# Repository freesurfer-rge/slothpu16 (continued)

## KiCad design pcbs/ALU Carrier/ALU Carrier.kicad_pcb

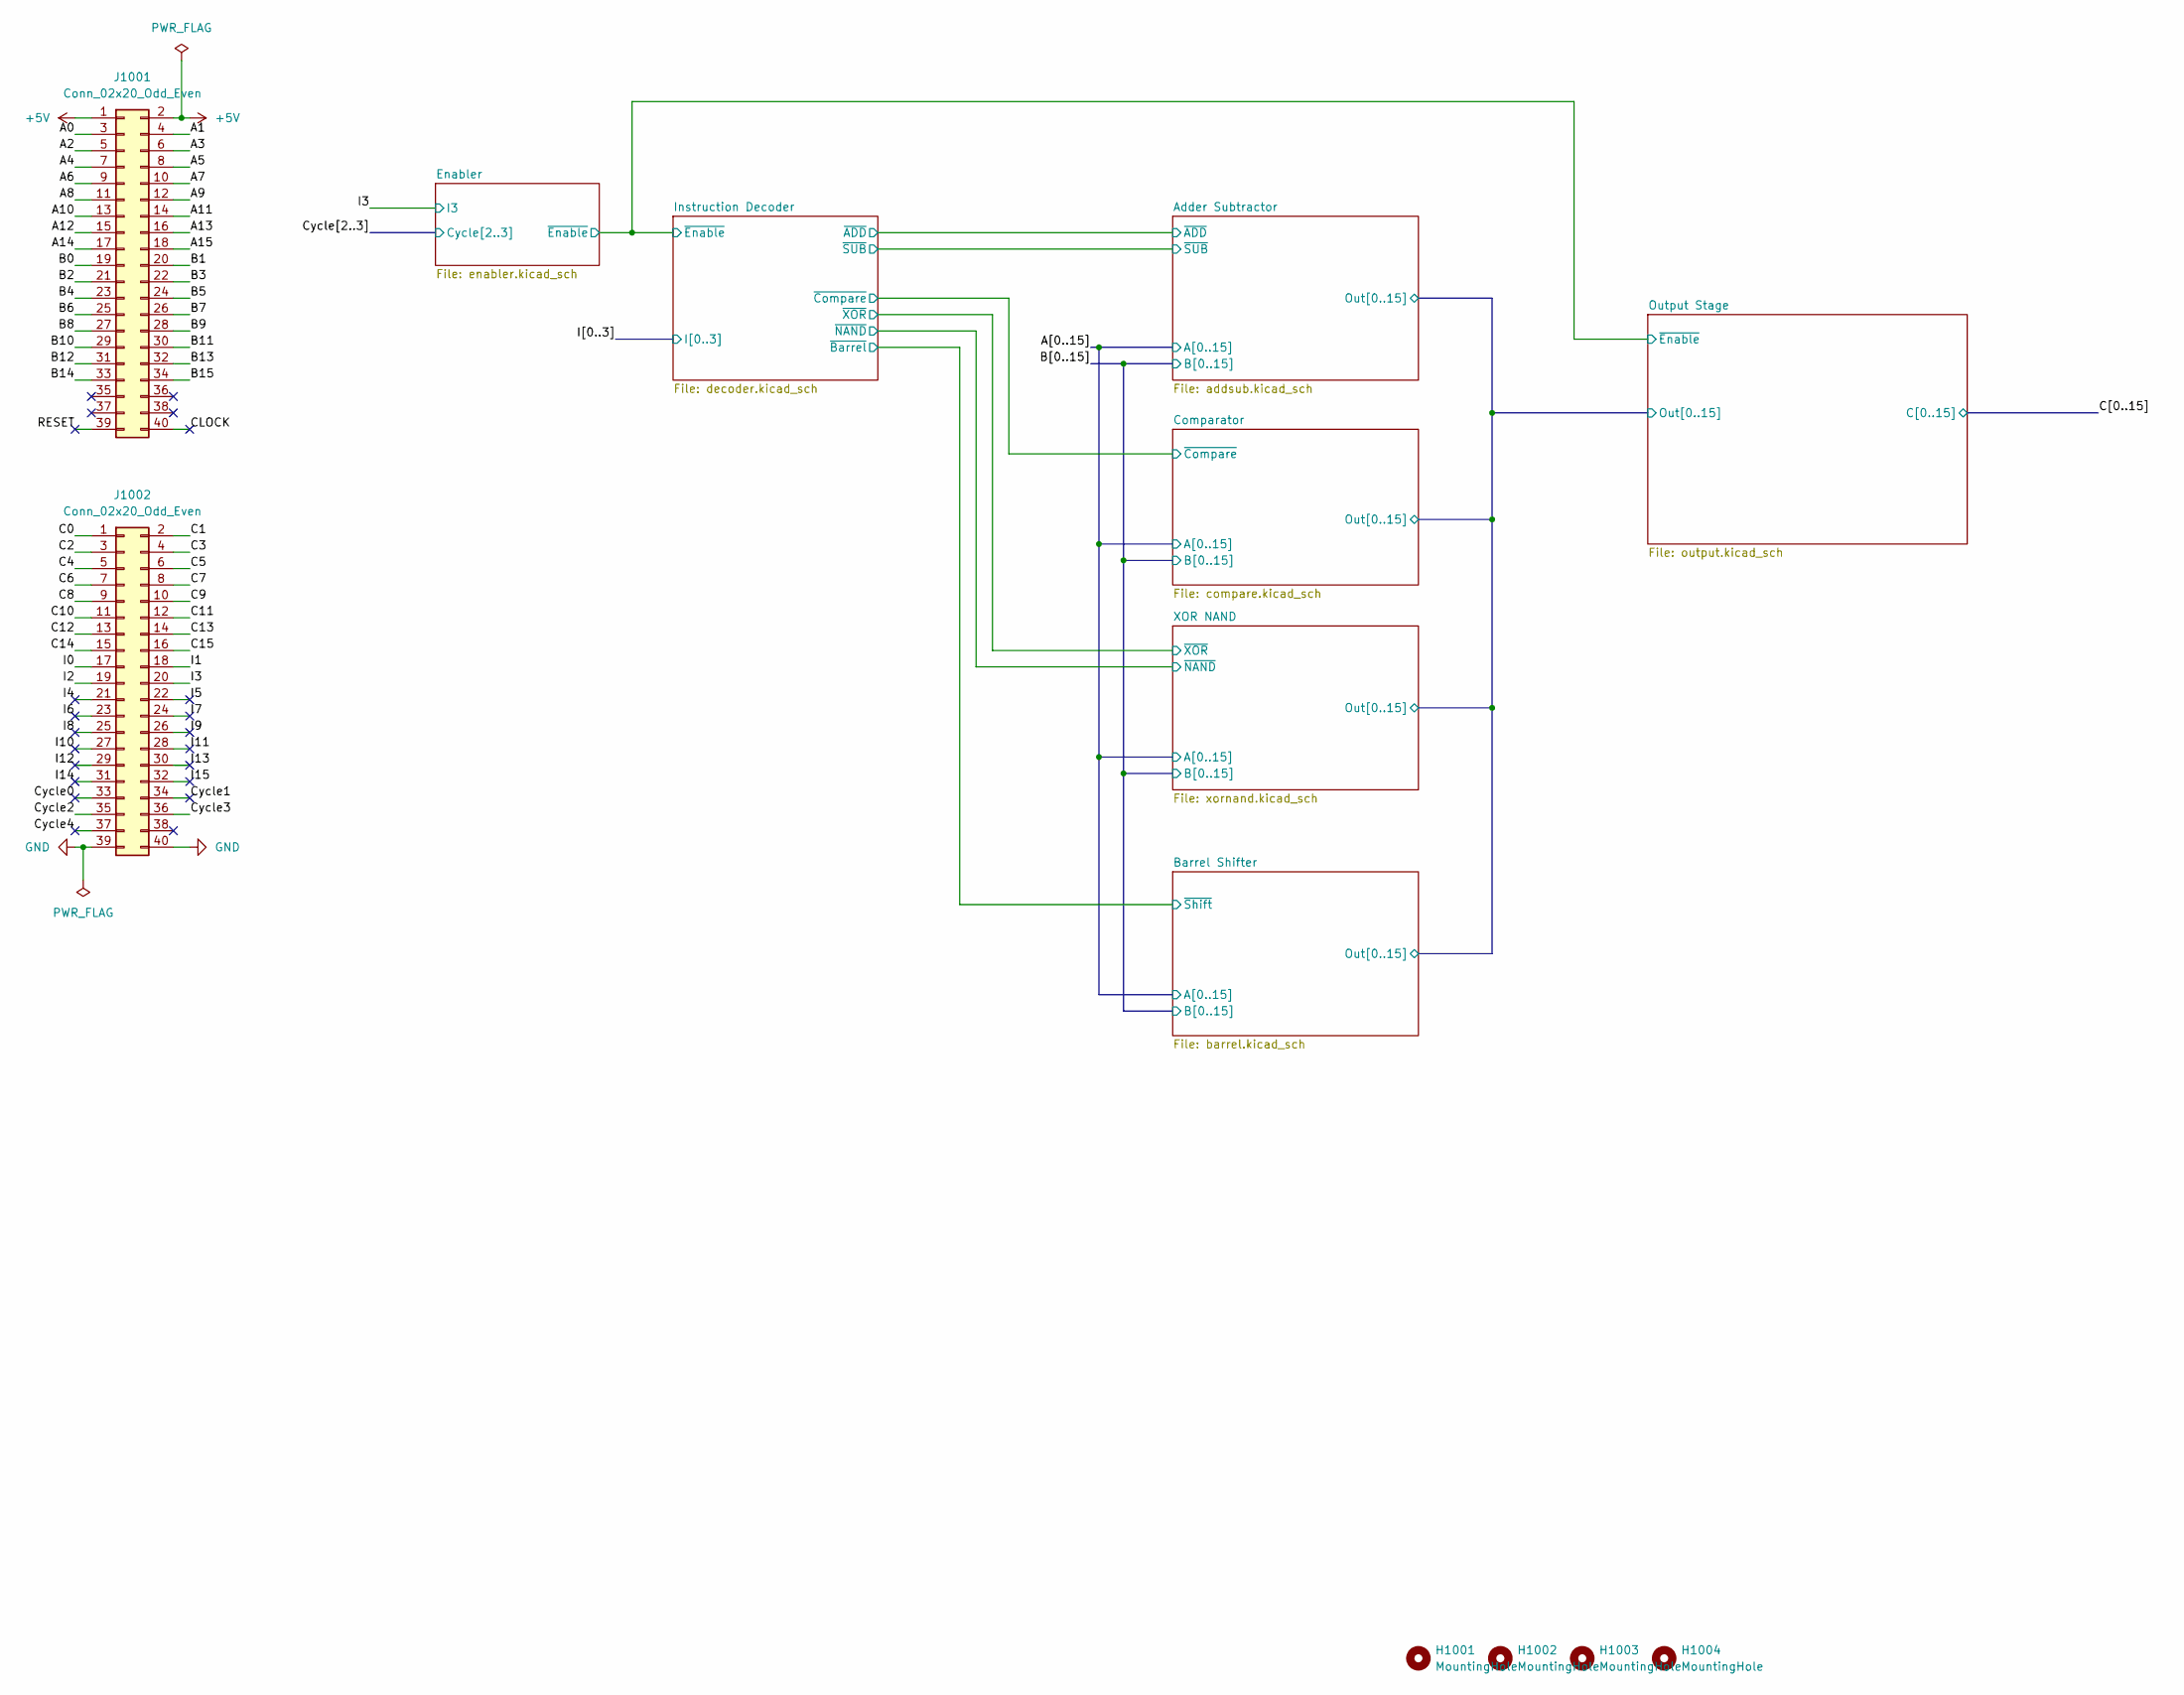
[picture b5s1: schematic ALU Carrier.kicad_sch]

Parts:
H1001, H1002, H1003, H1004: MountingHole; MountingHole_2.7mm_M2.5_ISO7380
J1001, J1002: Conn_02x20_Odd_Even; PinHeader_2x20_P2.54mm_Vertical

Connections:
+5V: J1001.1, J1001.2; also elsewhere on the board
/A0: J1001.3; also elsewhere on the board
/A1: J1001.4; also elsewhere on the board
/A2: J1001.5; also elsewhere on the board
/A3: J1001.6; also elsewhere on the board
/A4: J1001.7; also elsewhere on the board
/A5: J1001.8; also elsewhere on the board
/A6: J1001.9; also elsewhere on the board
/A7: J1001.10; also elsewhere on the board
/A8: J1001.11; also elsewhere on the board
/A9: J1001.12; also elsewhere on the board
/A10: J1001.13; also elsewhere on the board
/A11: J1001.14; also elsewhere on the board
/A12: J1001.15; also elsewhere on the board
/A13: J1001.16; also elsewhere on the board
/A14: J1001.17; also elsewhere on the board
/A15: J1001.18; also elsewhere on the board
/B0: J1001.19; also elsewhere on the board
/B1: J1001.20; also elsewhere on the board
/B2: J1001.21; also elsewhere on the board
/B3: J1001.22; also elsewhere on the board
/B4: J1001.23; also elsewhere on the board
/B5: J1001.24; also elsewhere on the board
/B6: J1001.25; also elsewhere on the board
/B7: J1001.26; also elsewhere on the board
/B8: J1001.27; also elsewhere on the board
/B9: J1001.28; also elsewhere on the board
/B10: J1001.29; also elsewhere on the board
/B11: J1001.30; also elsewhere on the board
/B12: J1001.31; also elsewhere on the board
/B13: J1001.32; also elsewhere on the board
/B14: J1001.33; also elsewhere on the board
/B15: J1001.34; also elsewhere on the board
/C0: J1002.1; also elsewhere on the board
/C1: J1002.2; also elsewhere on the board
/C2: J1002.3; also elsewhere on the board
/C3: J1002.4; also elsewhere on the board
/C4: J1002.5; also elsewhere on the board
/C5: J1002.6; also elsewhere on the board
/C6: J1002.7; also elsewhere on the board
/C7: J1002.8; also elsewhere on the board
/C8: J1002.9; also elsewhere on the board
/C9: J1002.10; also elsewhere on the board
/C10: J1002.11; also elsewhere on the board
/C11: J1002.12; also elsewhere on the board
/C12: J1002.13; also elsewhere on the board
/C13: J1002.14; also elsewhere on the board
/C14: J1002.15; also elsewhere on the board
/C15: J1002.16; also elsewhere on the board
/CLOCK: J1001.40
/Cycle0: J1002.33
/Cycle1: J1002.34
/Cycle2: J1002.35; also elsewhere on the board
/Cycle3: J1002.36; also elsewhere on the board
/Cycle4: J1002.37
/I0: J1002.17; also elsewhere on the board
/I1: J1002.18; also elsewhere on the board
/I2: J1002.19; also elsewhere on the board
/I3: J1002.20; also elsewhere on the board
/I4: J1002.21
/I5: J1002.22
/I6: J1002.23
/I7: J1002.24
/I8: J1002.25
/I9: J1002.26
/I10: J1002.27
/I11: J1002.28
/I12: J1002.29
/I13: J1002.30
/I14: J1002.31
/I15: J1002.32
/RESET: J1001.39
GND: J1002.39, J1002.40; also elsewhere on the board

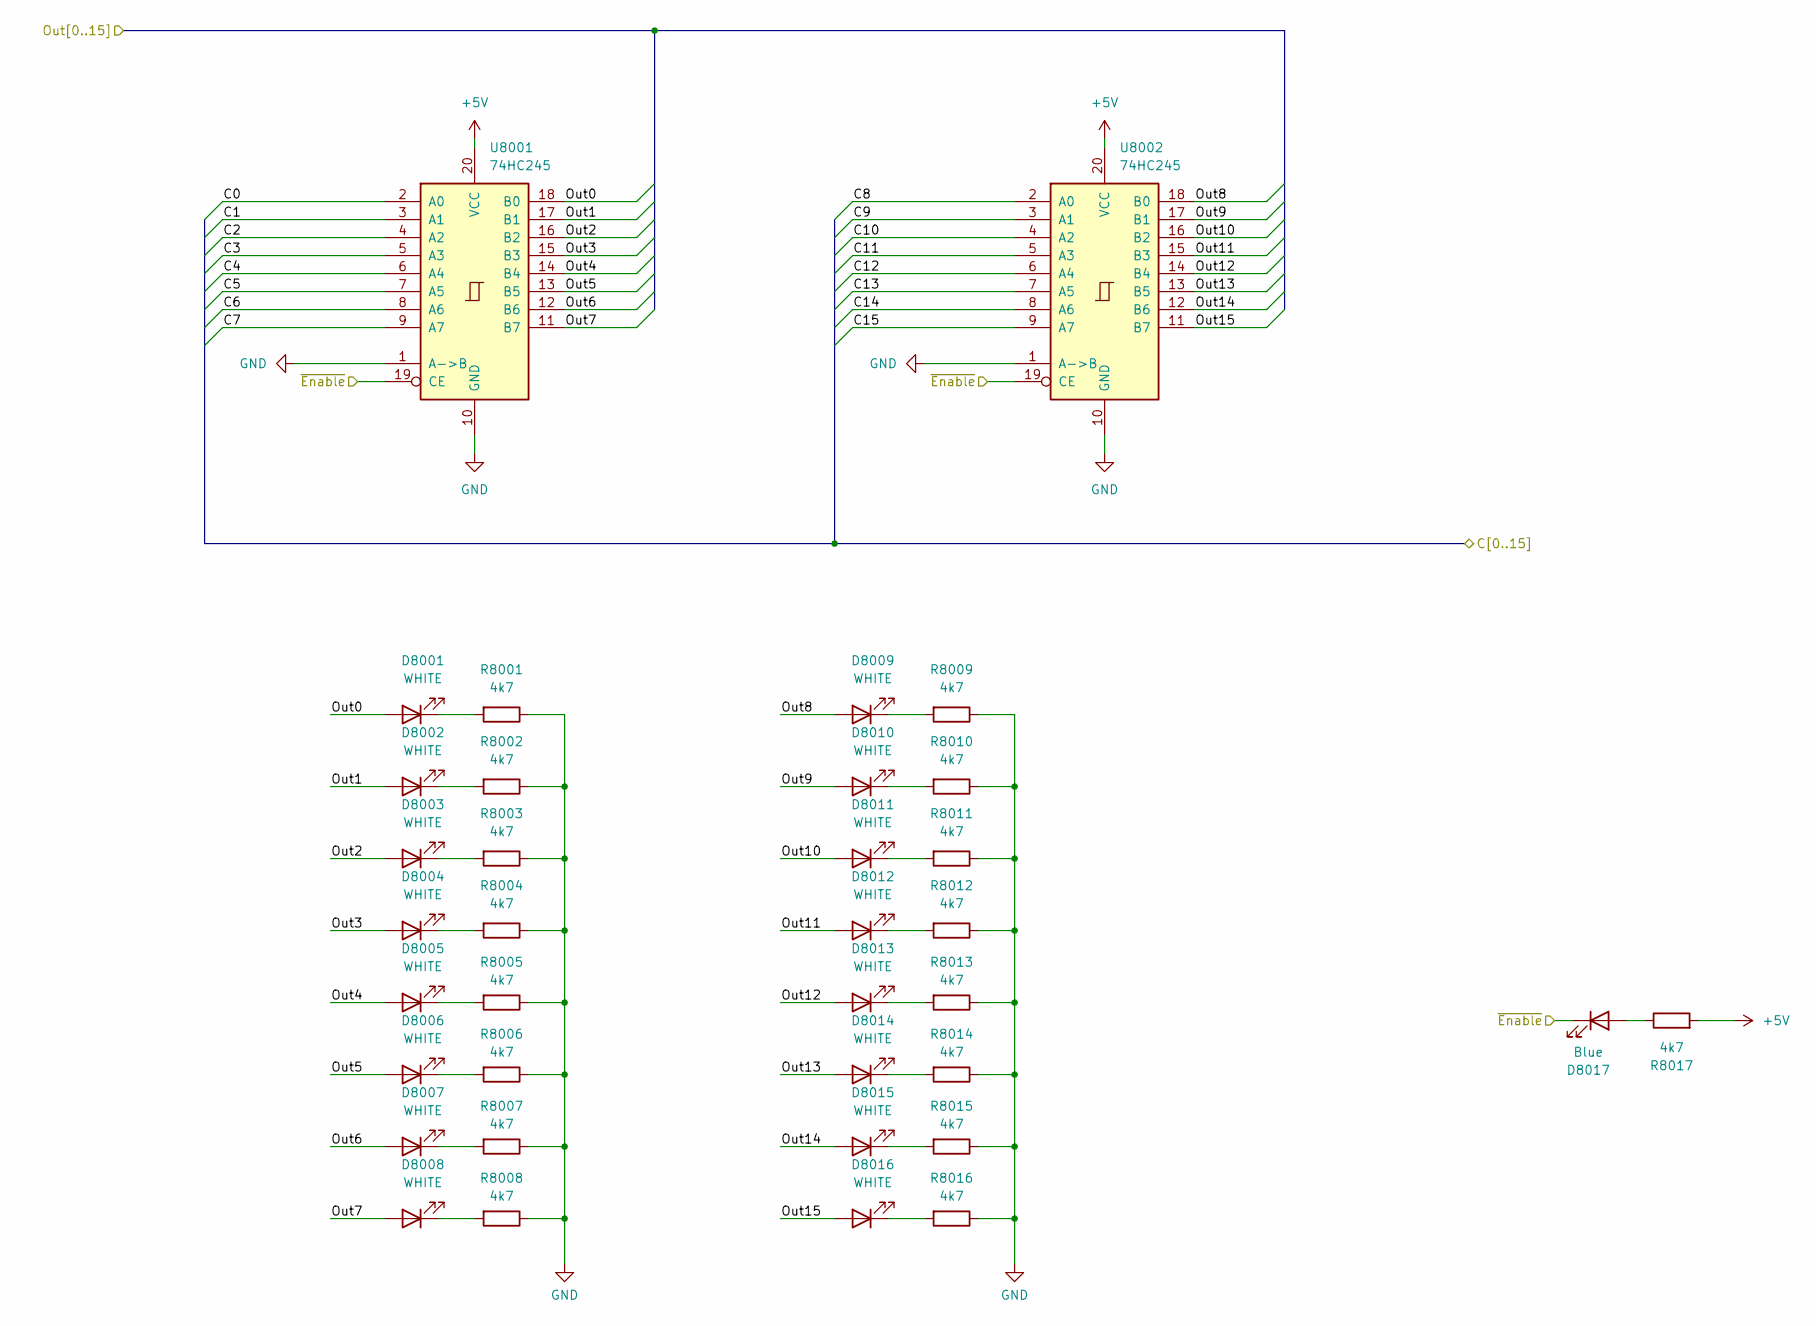
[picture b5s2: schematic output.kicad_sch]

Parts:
D8001, D8002, D8003, D8004, D8005, D8006, D8007, D8008, D8009, D8010, D8011, D8012, D8013, D8014, D8015, D8016: WHITE; LED_0603_1608Metric; LCSC C2290
D8017: Blue; LED_0603_1608Metric; LCSC C72041
R8001, R8002, R8003, R8004, R8005, R8006, R8007, R8008, R8009, R8010, R8011, R8012, R8013, R8014, R8015, R8016, R8017: 4k7; R_0603_1608Metric; LCSC C23162
U8001, U8002: 74HC245; SOIC-20W_7.5x12.8mm_P1.27mm; LCSC C5625

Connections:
+5V: R8017.2, U8001.20 (VCC), U8002.20 (VCC); also elsewhere on the board
/Adder Subtractor/Out0: D8001.2 (A), U8001.18 (B0); also elsewhere on the board
/Adder Subtractor/Out1: D8002.2 (A), U8001.17 (B1); also elsewhere on the board
/Adder Subtractor/Out2: D8003.2 (A), U8001.16 (B2); also elsewhere on the board
/Adder Subtractor/Out3: D8004.2 (A), U8001.15 (B3); also elsewhere on the board
/Adder Subtractor/Out4: D8005.2 (A), U8001.14 (B4); also elsewhere on the board
/Adder Subtractor/Out5: D8006.2 (A), U8001.13 (B5); also elsewhere on the board
/Adder Subtractor/Out6: D8007.2 (A), U8001.12 (B6); also elsewhere on the board
/Adder Subtractor/Out7: D8008.2 (A), U8001.11 (B7); also elsewhere on the board
/Adder Subtractor/Out8: D8009.2 (A), U8002.18 (B0); also elsewhere on the board
/Adder Subtractor/Out9: D8010.2 (A), U8002.17 (B1); also elsewhere on the board
/Adder Subtractor/Out10: D8011.2 (A), U8002.16 (B2); also elsewhere on the board
/Adder Subtractor/Out11: D8012.2 (A), U8002.15 (B3); also elsewhere on the board
/Adder Subtractor/Out12: D8013.2 (A), U8002.14 (B4); also elsewhere on the board
/Adder Subtractor/Out13: D8014.2 (A), U8002.13 (B5); also elsewhere on the board
/Adder Subtractor/Out14: D8015.2 (A), U8002.12 (B6); also elsewhere on the board
/Adder Subtractor/Out15: D8016.2 (A), U8002.11 (B7); also elsewhere on the board
/C0: U8001.2 (A0); also elsewhere on the board
/C1: U8001.3 (A1); also elsewhere on the board
/C2: U8001.4 (A2); also elsewhere on the board
/C3: U8001.5 (A3); also elsewhere on the board
/C4: U8001.6 (A4); also elsewhere on the board
/C5: U8001.7 (A5); also elsewhere on the board
/C6: U8001.8 (A6); also elsewhere on the board
/C7: U8001.9 (A7); also elsewhere on the board
/C8: U8002.2 (A0); also elsewhere on the board
/C9: U8002.3 (A1); also elsewhere on the board
/C10: U8002.4 (A2); also elsewhere on the board
/C11: U8002.5 (A3); also elsewhere on the board
/C12: U8002.6 (A4); also elsewhere on the board
/C13: U8002.7 (A5); also elsewhere on the board
/C14: U8002.8 (A6); also elsewhere on the board
/C15: U8002.9 (A7); also elsewhere on the board
/Enabler/~Enable: D8017.1 (K), U8001.19 (CE), U8002.19 (CE); also elsewhere on the board
GND: R8001.1, R8002.1, R8003.1, R8004.1, R8005.1, R8006.1, R8007.1, R8008.1, R8009.1, R8010.1, R8011.1, R8012.1, R8013.1, R8014.1, R8015.1, R8016.1, U8001.1 (A->B), U8001.10 (GND), U8002.1 (A->B), U8002.10 (GND); also elsewhere on the board
unnamed: D8001.1 (K), R8001.2
unnamed: D8002.1 (K), R8002.2
unnamed: D8003.1 (K), R8003.2
unnamed: D8004.1 (K), R8004.2
unnamed: D8005.1 (K), R8005.2
unnamed: D8006.1 (K), R8006.2
unnamed: D8007.1 (K), R8007.2
unnamed: D8008.1 (K), R8008.2
unnamed: D8009.1 (K), R8009.2
unnamed: D8010.1 (K), R8010.2
unnamed: D8011.1 (K), R8011.2
unnamed: D8012.1 (K), R8012.2
unnamed: D8013.1 (K), R8013.2
unnamed: D8014.1 (K), R8014.2
unnamed: D8015.1 (K), R8015.2
unnamed: D8016.1 (K), R8016.2
unnamed: D8017.2 (A), R8017.1

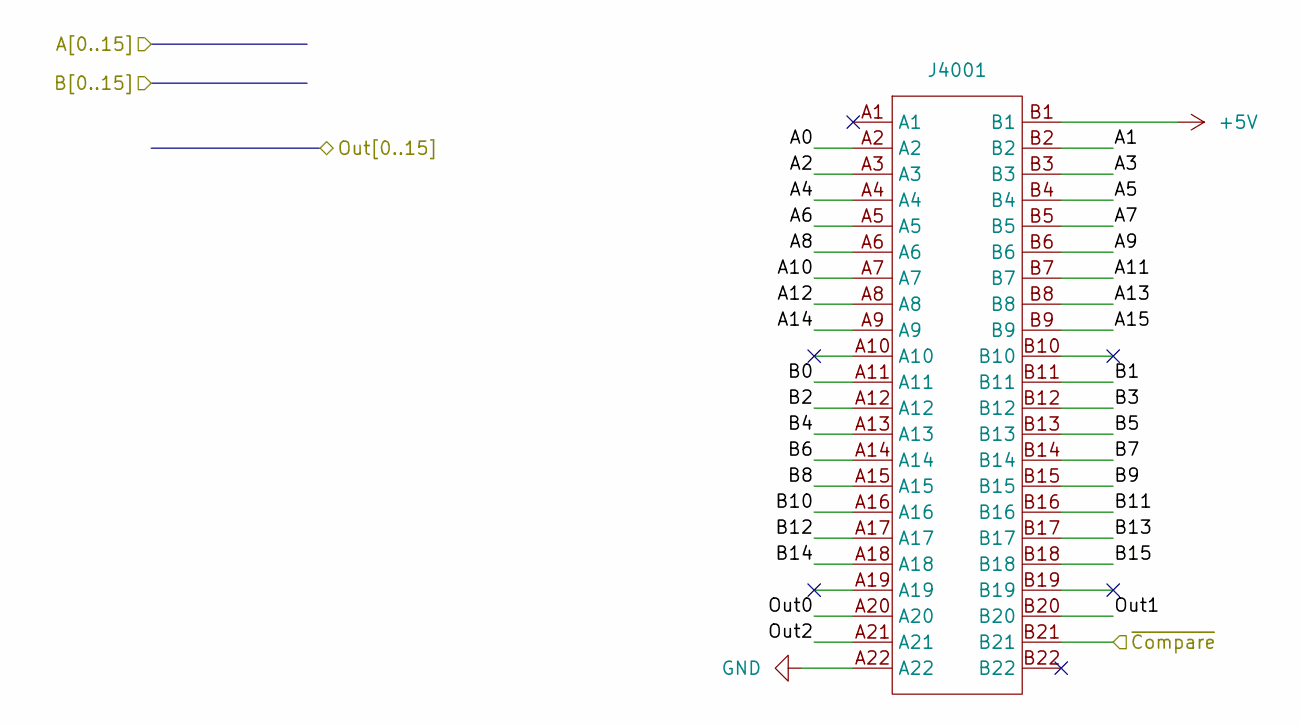
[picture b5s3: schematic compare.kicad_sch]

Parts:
J4001: TE-5530843-4-Mount

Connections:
+5V: J4001.B1; also elsewhere on the board
/A0: J4001.A2; also elsewhere on the board
/A1: J4001.B2; also elsewhere on the board
/A2: J4001.A3; also elsewhere on the board
/A3: J4001.B3; also elsewhere on the board
/A4: J4001.A4; also elsewhere on the board
/A5: J4001.B4; also elsewhere on the board
/A6: J4001.A5; also elsewhere on the board
/A7: J4001.B5; also elsewhere on the board
/A8: J4001.A6; also elsewhere on the board
/A9: J4001.B6; also elsewhere on the board
/A10: J4001.A7; also elsewhere on the board
/A11: J4001.B7; also elsewhere on the board
/A12: J4001.A8; also elsewhere on the board
/A13: J4001.B8; also elsewhere on the board
/A14: J4001.A9; also elsewhere on the board
/A15: J4001.B9; also elsewhere on the board
/Adder Subtractor/Out0: J4001.A20; also elsewhere on the board
/Adder Subtractor/Out1: J4001.B20; also elsewhere on the board
/Adder Subtractor/Out2: J4001.A21; also elsewhere on the board
/B0: J4001.A11; also elsewhere on the board
/B1: J4001.B11; also elsewhere on the board
/B2: J4001.A12; also elsewhere on the board
/B3: J4001.B12; also elsewhere on the board
/B4: J4001.A13; also elsewhere on the board
/B5: J4001.B13; also elsewhere on the board
/B6: J4001.A14; also elsewhere on the board
/B7: J4001.B14; also elsewhere on the board
/B8: J4001.A15; also elsewhere on the board
/B9: J4001.B15; also elsewhere on the board
/B10: J4001.A16; also elsewhere on the board
/B11: J4001.B16; also elsewhere on the board
/B12: J4001.A17; also elsewhere on the board
/B13: J4001.B17; also elsewhere on the board
/B14: J4001.A18; also elsewhere on the board
/B15: J4001.B18; also elsewhere on the board
/Comparator/~Compare: J4001.B21; also elsewhere on the board
GND: J4001.A22; also elsewhere on the board

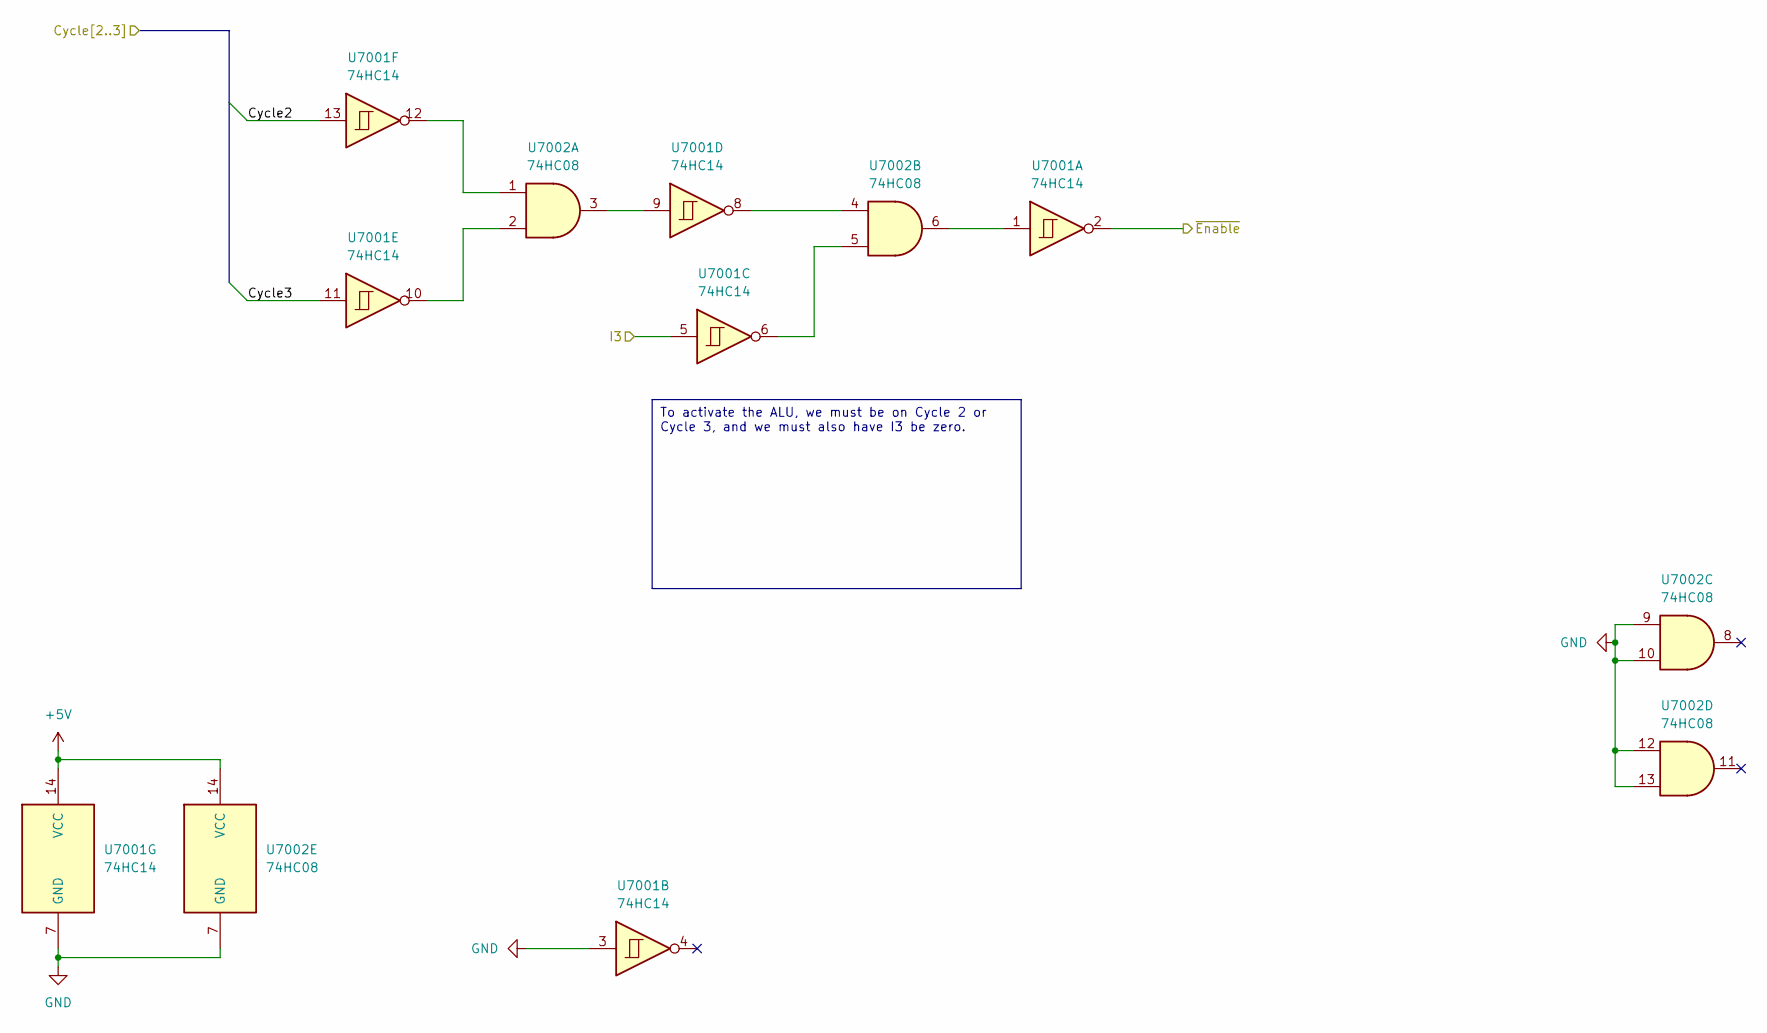
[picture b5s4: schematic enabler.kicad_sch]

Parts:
U7001: 74HC14; SOIC-14_3.9x8.7mm_P1.27mm; LCSC C5605
U7002: 74HC08; SOIC-14_3.9x8.7mm_P1.27mm; LCSC C5593

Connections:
+5V: U7001.14 (VCC), U7002.14 (VCC); also elsewhere on the board
/Cycle2: U7001.13; also elsewhere on the board
/Cycle3: U7001.11; also elsewhere on the board
/Enabler/~Enable: U7001.2; also elsewhere on the board
/I3: U7001.5; also elsewhere on the board
GND: U7001.3, U7001.7 (GND), U7002.7 (GND), U7002.9, U7002.10, U7002.12, U7002.13; also elsewhere on the board
unnamed: U7001.1, U7002.6
unnamed: U7001.6, U7002.5
unnamed: U7001.8, U7002.4
unnamed: U7001.9, U7002.3
unnamed: U7001.10, U7002.2
unnamed: U7001.12, U7002.1

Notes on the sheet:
To activate the ALU, we must be on Cycle 2 or Cycle 3, and we must also have I3 be zero.

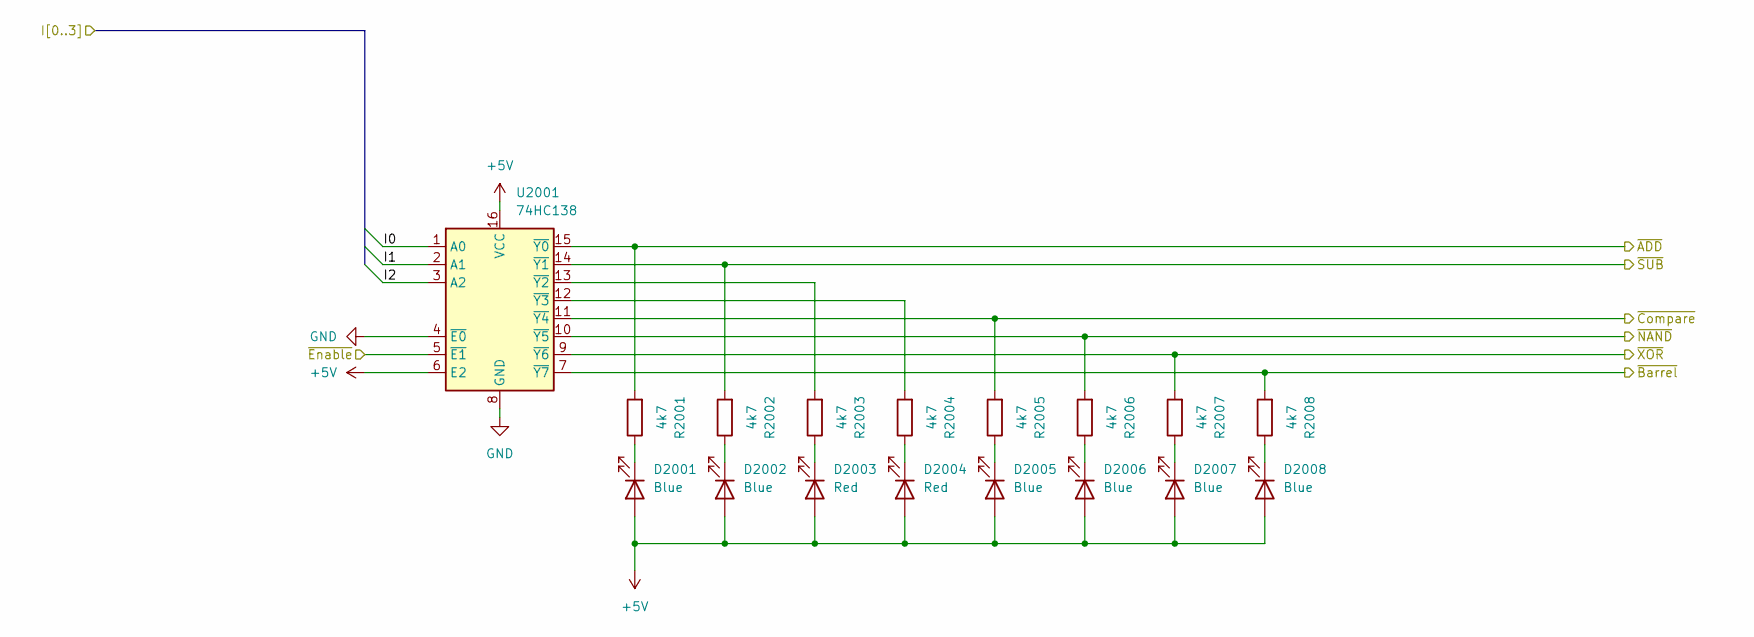
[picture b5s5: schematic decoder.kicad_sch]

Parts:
D2001, D2002, D2005, D2006, D2007, D2008: Blue; LED_0603_1608Metric; LCSC C72041
D2003, D2004: Red; LED_0603_1608Metric; LCSC C2286
R2001, R2002, R2003, R2004, R2005, R2006, R2007, R2008: 4k7; R_0603_1608Metric; LCSC C23162
U2001: 74HC138; DIP-16_W7.62mm_Socket

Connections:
+5V: D2001.2 (A), D2002.2 (A), D2003.2 (A), D2004.2 (A), D2005.2 (A), D2006.2 (A), D2007.2 (A), D2008.2 (A), U2001.6 (E2), U2001.16 (VCC); also elsewhere on the board
/Adder Subtractor/~ADD: R2001.2, U2001.15 (~Y0); also elsewhere on the board
/Adder Subtractor/~SUB: R2002.2, U2001.14 (~Y1); also elsewhere on the board
/Barrel Shifter/~Shift: R2008.2, U2001.7 (~Y7); also elsewhere on the board
/Comparator/~Compare: R2005.2, U2001.11 (~Y4); also elsewhere on the board
/Enabler/~Enable: U2001.5 (~E1); also elsewhere on the board
/I0: U2001.1 (A0); also elsewhere on the board
/I1: U2001.2 (A1); also elsewhere on the board
/I2: U2001.3 (A2); also elsewhere on the board
/Instruction Decoder/~NAND: R2006.2, U2001.10 (~Y5); also elsewhere on the board
/Instruction Decoder/~XOR: R2007.2, U2001.9 (~Y6); also elsewhere on the board
GND: U2001.4 (~E0), U2001.8 (GND); also elsewhere on the board
unnamed: D2001.1 (K), R2001.1
unnamed: D2002.1 (K), R2002.1
unnamed: D2003.1 (K), R2003.1
unnamed: D2004.1 (K), R2004.1
unnamed: D2005.1 (K), R2005.1
unnamed: D2006.1 (K), R2006.1
unnamed: D2007.1 (K), R2007.1
unnamed: D2008.1 (K), R2008.1
unnamed: R2003.2, U2001.13 (~Y2)
unnamed: R2004.2, U2001.12 (~Y3)

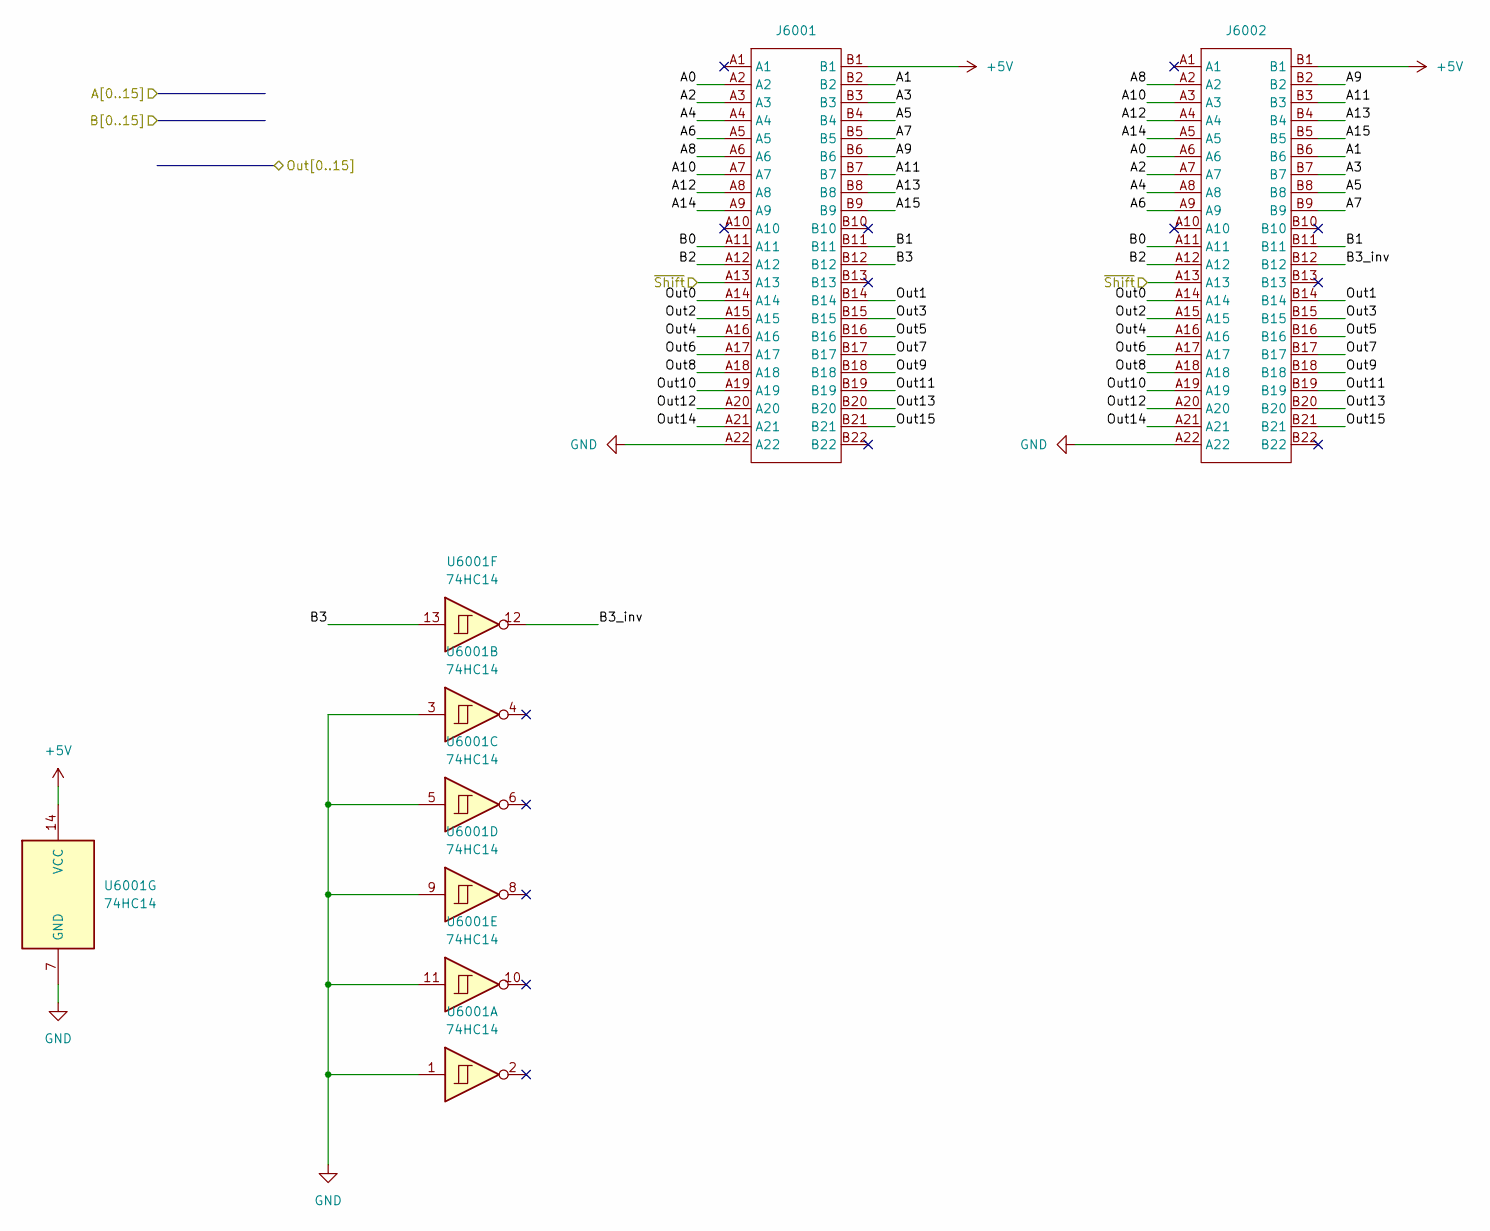
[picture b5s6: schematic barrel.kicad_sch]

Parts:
J6001, J6002: TE-5530843-4-Mount
U6001: 74HC14; SOIC-14_3.9x8.7mm_P1.27mm; LCSC C5605

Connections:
+5V: J6001.B1, J6002.B1, U6001.14 (VCC); also elsewhere on the board
/A0: J6001.A2, J6002.A6; also elsewhere on the board
/A1: J6001.B2, J6002.B6; also elsewhere on the board
/A2: J6001.A3, J6002.A7; also elsewhere on the board
/A3: J6001.B3, J6002.B7; also elsewhere on the board
/A4: J6001.A4, J6002.A8; also elsewhere on the board
/A5: J6001.B4, J6002.B8; also elsewhere on the board
/A6: J6001.A5, J6002.A9; also elsewhere on the board
/A7: J6001.B5, J6002.B9; also elsewhere on the board
/A8: J6001.A6, J6002.A2; also elsewhere on the board
/A9: J6001.B6, J6002.B2; also elsewhere on the board
/A10: J6001.A7, J6002.A3; also elsewhere on the board
/A11: J6001.B7, J6002.B3; also elsewhere on the board
/A12: J6001.A8, J6002.A4; also elsewhere on the board
/A13: J6001.B8, J6002.B4; also elsewhere on the board
/A14: J6001.A9, J6002.A5; also elsewhere on the board
/A15: J6001.B9, J6002.B5; also elsewhere on the board
/Adder Subtractor/Out0: J6001.A14, J6002.A14; also elsewhere on the board
/Adder Subtractor/Out1: J6001.B14, J6002.B14; also elsewhere on the board
/Adder Subtractor/Out2: J6001.A15, J6002.A15; also elsewhere on the board
/Adder Subtractor/Out3: J6001.B15, J6002.B15; also elsewhere on the board
/Adder Subtractor/Out4: J6001.A16, J6002.A16; also elsewhere on the board
/Adder Subtractor/Out5: J6001.B16, J6002.B16; also elsewhere on the board
/Adder Subtractor/Out6: J6001.A17, J6002.A17; also elsewhere on the board
/Adder Subtractor/Out7: J6001.B17, J6002.B17; also elsewhere on the board
/Adder Subtractor/Out8: J6001.A18, J6002.A18; also elsewhere on the board
/Adder Subtractor/Out9: J6001.B18, J6002.B18; also elsewhere on the board
/Adder Subtractor/Out10: J6001.A19, J6002.A19; also elsewhere on the board
/Adder Subtractor/Out11: J6001.B19, J6002.B19; also elsewhere on the board
/Adder Subtractor/Out12: J6001.A20, J6002.A20; also elsewhere on the board
/Adder Subtractor/Out13: J6001.B20, J6002.B20; also elsewhere on the board
/Adder Subtractor/Out14: J6001.A21, J6002.A21; also elsewhere on the board
/Adder Subtractor/Out15: J6001.B21, J6002.B21; also elsewhere on the board
/B0: J6001.A11, J6002.A11; also elsewhere on the board
/B1: J6001.B11, J6002.B11; also elsewhere on the board
/B2: J6001.A12, J6002.A12; also elsewhere on the board
/B3: J6001.B12, U6001.13; also elsewhere on the board
/Barrel Shifter/B3_inv: J6002.B12, U6001.12
/Barrel Shifter/~Shift: J6001.A13, J6002.A13; also elsewhere on the board
GND: J6001.A22, J6002.A22, U6001.1, U6001.3, U6001.5, U6001.7 (GND), U6001.9, U6001.11; also elsewhere on the board

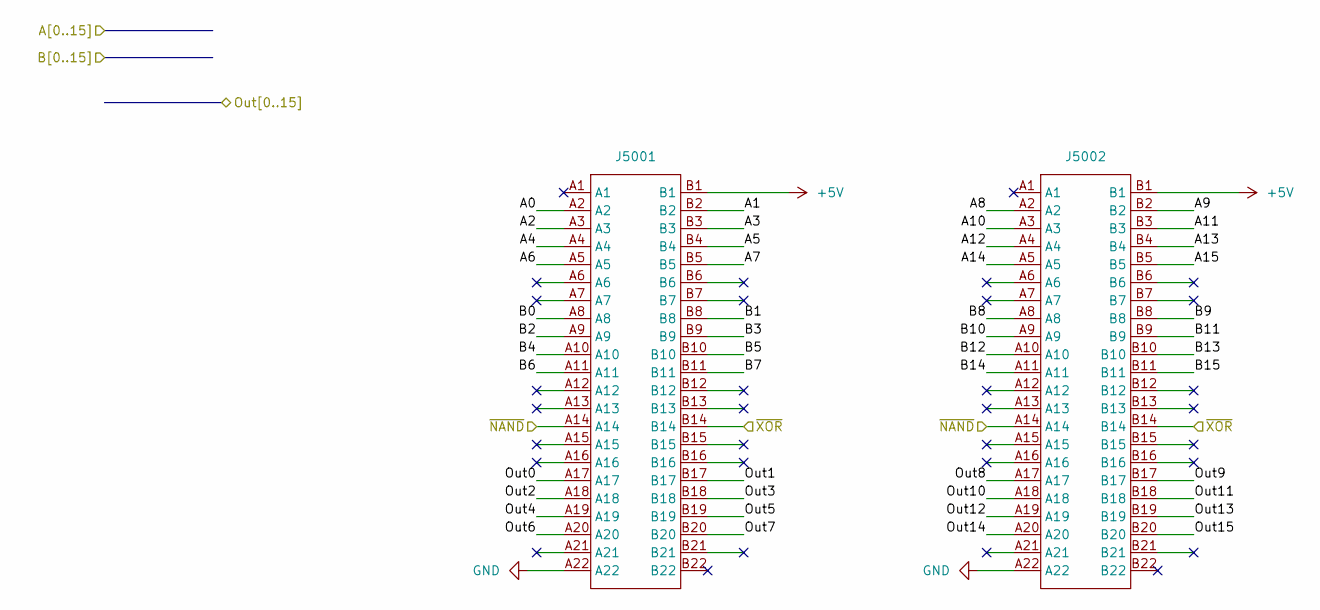
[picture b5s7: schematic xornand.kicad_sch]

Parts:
J5001, J5002: TE-5530843-4-Mount

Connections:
+5V: J5001.B1, J5002.B1; also elsewhere on the board
/A0: J5001.A2; also elsewhere on the board
/A1: J5001.B2; also elsewhere on the board
/A2: J5001.A3; also elsewhere on the board
/A3: J5001.B3; also elsewhere on the board
/A4: J5001.A4; also elsewhere on the board
/A5: J5001.B4; also elsewhere on the board
/A6: J5001.A5; also elsewhere on the board
/A7: J5001.B5; also elsewhere on the board
/A8: J5002.A2; also elsewhere on the board
/A9: J5002.B2; also elsewhere on the board
/A10: J5002.A3; also elsewhere on the board
/A11: J5002.B3; also elsewhere on the board
/A12: J5002.A4; also elsewhere on the board
/A13: J5002.B4; also elsewhere on the board
/A14: J5002.A5; also elsewhere on the board
/A15: J5002.B5; also elsewhere on the board
/Adder Subtractor/Out0: J5001.A17; also elsewhere on the board
/Adder Subtractor/Out1: J5001.B17; also elsewhere on the board
/Adder Subtractor/Out2: J5001.A18; also elsewhere on the board
/Adder Subtractor/Out3: J5001.B18; also elsewhere on the board
/Adder Subtractor/Out4: J5001.A19; also elsewhere on the board
/Adder Subtractor/Out5: J5001.B19; also elsewhere on the board
/Adder Subtractor/Out6: J5001.A20; also elsewhere on the board
/Adder Subtractor/Out7: J5001.B20; also elsewhere on the board
/Adder Subtractor/Out8: J5002.A17; also elsewhere on the board
/Adder Subtractor/Out9: J5002.B17; also elsewhere on the board
/Adder Subtractor/Out10: J5002.A18; also elsewhere on the board
/Adder Subtractor/Out11: J5002.B18; also elsewhere on the board
/Adder Subtractor/Out12: J5002.A19; also elsewhere on the board
/Adder Subtractor/Out13: J5002.B19; also elsewhere on the board
/Adder Subtractor/Out14: J5002.A20; also elsewhere on the board
/Adder Subtractor/Out15: J5002.B20; also elsewhere on the board
/B0: J5001.A8; also elsewhere on the board
/B1: J5001.B8; also elsewhere on the board
/B2: J5001.A9; also elsewhere on the board
/B3: J5001.B9; also elsewhere on the board
/B4: J5001.A10; also elsewhere on the board
/B5: J5001.B10; also elsewhere on the board
/B6: J5001.A11; also elsewhere on the board
/B7: J5001.B11; also elsewhere on the board
/B8: J5002.A8; also elsewhere on the board
/B9: J5002.B8; also elsewhere on the board
/B10: J5002.A9; also elsewhere on the board
/B11: J5002.B9; also elsewhere on the board
/B12: J5002.A10; also elsewhere on the board
/B13: J5002.B10; also elsewhere on the board
/B14: J5002.A11; also elsewhere on the board
/B15: J5002.B11; also elsewhere on the board
/Instruction Decoder/~NAND: J5001.A14, J5002.A14; also elsewhere on the board
/Instruction Decoder/~XOR: J5001.B14, J5002.B14; also elsewhere on the board
GND: J5001.A22, J5002.A22; also elsewhere on the board
